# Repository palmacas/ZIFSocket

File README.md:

# ZIF Socket

This board works as adapter to program PIC microcontrollers using the PICKit2 or PICKit3. The ZIF_Distribution folder contains images with the ICs and jumpers distribution on the ZIF socket depending on the PIC type.

---
More information:\
[Zócalo ZIF – PICKit 2 y PICKit 3 [Spanish]](https://palmacas.com/zocalo-zif-pickit-2-y-pickit-3/)  
[Distribución de Zócalo ZIF [Spanish]](https://palmacas.com/distribucion-zocalo-zif/)  
[PICKit 2 Clone Zócalo ZIF [Spanish]](https://palmacas.com/pickit-2-clone-zocalo-zif/)  
[PICKit 2 Clone ICSP [Spanish]](https://palmacas.com/pickit-2-clone-icsp/)

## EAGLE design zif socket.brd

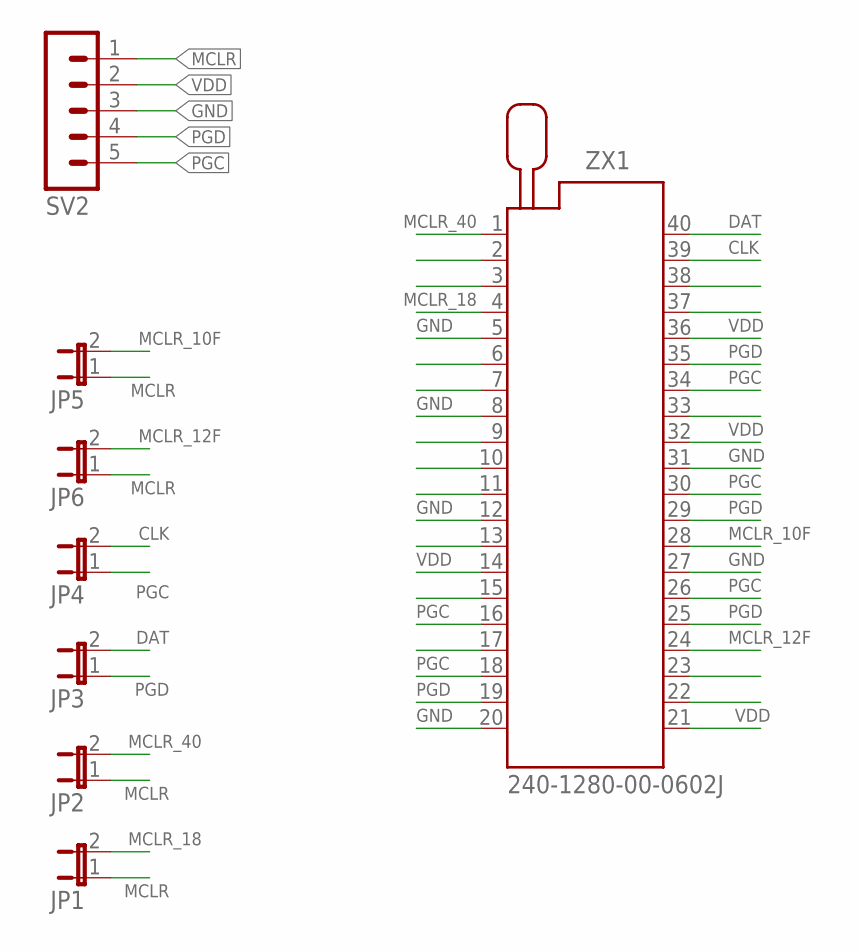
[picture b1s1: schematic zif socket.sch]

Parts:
JP1, JP2, JP3, JP4, JP5, JP6: JP1E; JP1
SV2: MA05-1
ZX1: 240-1280-00-0602J

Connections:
CLK: JP4.2, ZX1.39
DAT: JP3.2, ZX1.40
GND: SV2.3, ZX1.5, ZX1.8, ZX1.12, ZX1.20, ZX1.27, ZX1.31
MCLR: JP1.1, JP2.1, JP5.1, JP6.1, SV2.1
MCLR_10F: JP5.2, ZX1.28
MCLR_12F: JP6.2, ZX1.24
MCLR_18: JP1.2, ZX1.4
MCLR_40: JP2.2, ZX1.1
PGC: JP4.1, SV2.5, ZX1.16, ZX1.18, ZX1.26, ZX1.30, ZX1.34
PGD: JP3.1, SV2.4, ZX1.19, ZX1.25, ZX1.29, ZX1.35
VDD: SV2.2, ZX1.14, ZX1.21, ZX1.32, ZX1.36

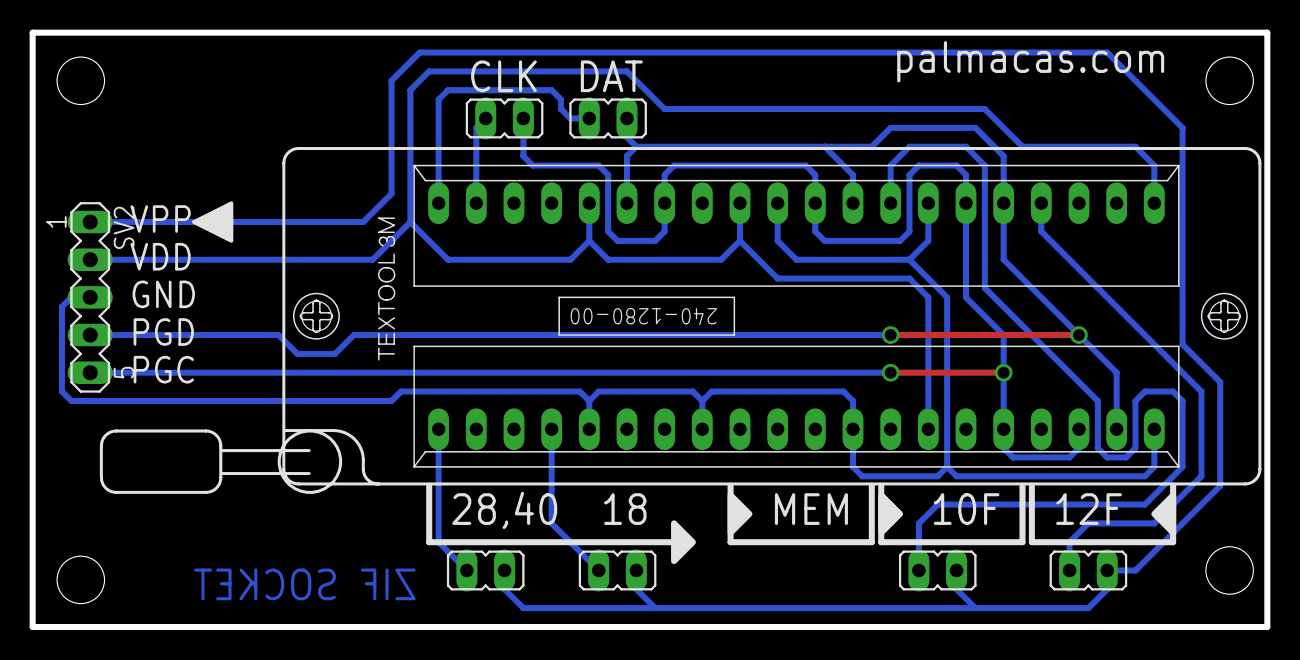
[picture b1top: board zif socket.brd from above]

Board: 2 copper layers, 83.3 x 40.1 mm, 8 parts (0 on the bottom side), 11 nets.

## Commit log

2020-06-02 ZIF distribution images
2020-06-03 Update LICENSE
